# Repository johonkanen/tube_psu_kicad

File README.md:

# tube_psu_kicad

Migration of the **tube_power_5_1** board ("Tube power supply", V5.1) from Proteus 8.12
to KiCad 10. The KiCad schematic is redrawn from the Proteus PDF, and the PCB is rebuilt
from the Proteus gerbers, so that every pad, track, via and pour carries a net from the new
schematic. The goal is a KiCad design that is **electrically identical** to the Proteus
original.

The Proteus project file is binary and cannot be read, so the IPC-D-356A netlist in the
CADCAM export is the reference: 193 nets, 315 parts, 1165 pad/via/hole records, each with
net, refdes, pin and coordinates. Every check in this repo compares against that file.

The method follows `tools/p2k/CONVERSION_PLAYBOOK.md`. The tools are the shared
[proteus2kicad](https://github.com/johonkanen/proteus2kicad) repository, a git submodule in
`tools/p2k` (clone with `git clone --recurse-submodules`, or run
`git submodule update --init`); everything specific to this board is in `p2k_config.py`.

- `PLAN.md`: the plan, inventory of the source files, risks and model usage.
- `STATUS.md`: what is done, the last verification output, findings about the original
  design, and what comes next.
- `next_prompt.md`: the prompt for the next work session, replaced at the end of every
  phase.

## Board

3D renders and copper layers of the 5.2 board `kicad_next/tube_psu_5_2.kicad_pcb` (6 layers, in work) and of the
5.1 board `kicad/tube_psu.kicad_pcb`, made by GitHub Actions on every board change
([kicad-board-plots](https://github.com/johonkanen/kicad-board-plots), `.github/workflows/board-plots.yml`;
the images live on the `renders` branch).

<!-- board-plots:start -->
<!-- Generated by kicad-board-plots; edits between these markers are overwritten. -->

### tube_psu_5_2

3D renders and copper layers of `kicad_next/tube_psu_5_2.kicad_pcb`, the layers in stack order without silkscreen. Plotted by [kicad-board-plots](https://github.com/johonkanen/kicad-board-plots) on each board change; the images live on the `renders` branch.

<table>
<tr>
<td align="center"><br><b>3D, top</b></td>
<td align="center"><br><b>3D, bottom (seen from below)</b></td>
</tr>
<tr>
<td align="center"><br><b>F.Cu: signal, Net-(RL1-COM), HEATER_HI_SOURCE, DHB_HI_SOURCE, GND, Q14_DRAIN and 28 more pours (top)</b></td>
<td align="center"><br><b>In1.Cu: IN2, ISO_GND, HT_GND, GND, RES_IN planes</b></td>
</tr>
<tr>
<td align="center"><br><b>In2.Cu: signal</b></td>
<td align="center"><br><b>In3.Cu: signal + plane, 5V, 6V3, 5V_ISOL, 15V_ISO_SEC, 15V and 1 more pours</b></td>
</tr>
<tr>
<td align="center"><br><b>In4.Cu: IN2, ISO_GND, GND, HT_GND planes</b></td>
<td align="center"><br><b>B.Cu: signal, 420V, PFC CURRENT 2+, ISO_GND, GND, 6V3 and 5 more pours (bottom, seen from the top)</b></td>
</tr>
</table>

### tube_psu

3D renders and copper layers of `kicad/tube_psu.kicad_pcb`, the layers in stack order without silkscreen. Plotted by [kicad-board-plots](https://github.com/johonkanen/kicad-board-plots) on each board change; the images live on the `renders` branch.

<table>
<tr>
<td align="center"><br><b>3D, top</b></td>
<td align="center"><br><b>3D, bottom (seen from below)</b></td>
</tr>
<tr>
<td align="center"><br><b>F.Cu: signal, Net-(RL1-COM), HEATER_HI_SOURCE, GND, Q14_DRAIN, AC1 and 28 more pours (top)</b></td>
<td align="center"><br><b>In1.Cu: signal, Q14_DRAIN, HT_GND, IN2, GND, Net-(L2-2) and 5 more pours</b></td>
</tr>
<tr>
<td align="center"><br><b>In2.Cu: signal, GND, IN2, L2_PRI2, Q14_DRAIN, DHB_HI_SOURCE_SEC and 3 more pours</b></td>
<td align="center"><br><b>B.Cu: signal, 420V, PFC CURRENT 2+, GND, ISO_GND, 15V and 6 more pours (bottom, seen from the top)</b></td>
</tr>
</table>

<!-- board-plots:end -->

## Layout

```
source/      Proteus exports (read-only): schematic PDF + page renders + text, the .pdsprj,
             cadcam/ = Gerber X2 export with drill gerbers and IPC-D-356A netlist (used),
             cadcam_rs274x/ = earlier RS-274X export with Excellon drill (cross-check only)
reference/   tables generated from the IPC netlist: pads (CSV/JSON), pin→net per part,
             pins per net
lib/         tube_psu.kicad_sym, part_map.csv, footprint_map.csv, tube_psu.pretty/ (all generated)
kicad/       KiCad project: root sheet + 11 sub-sheets (one per PDF page), tube_psu.kicad_pcb
             (generated by tools/make_pcb.sh)
p2k_config.py  board configuration of the proteus2kicad tools
tools/       check_all.sh, erc.sh, make_part_map.py, gen_symbols.py, sheets/ (one script per
             sheet), gen_footprints.py, make_pcb.sh, measure_gaps.py; p2k/ = proteus2kicad submodule
reports/     generated reports
```

## Phases

| Phase | Content | State |
|---|---|---|
| 0 | Tooling: KiCad AppImage wrappers, IPC-D-356A parser, reference tables, X2 export check | done |
| 1 | Schematic: part map, symbols, netlist comparison, skeleton; 11 sheets redrawn | done |
| 2 | Footprints, fitted to the IPC pads | done |
| 3 | PCB: board, tracks/vias from gerbers, nets, zones, DRC | done |
| 4 | Independent verification: gerber round trip, IPC-D-356 diff | – |

## Checks

`tools/check_all.sh` runs every check and prints `ALL CHECKS PASSED` or the failing steps.

| Script | Checks |
|---|---|
| `tools/p2k/bin/p2k ipc356 --check` | IPC parser counts and fix-ups; reference tables up to date |
| `tools/p2k/bin/p2k check_sources` | Gerber X2 flashes (vias, pads, free pads, holes) and drills vs IPC; outline |
| `tools/make_part_map.py --check` | `lib/part_map.csv` up to date with the .pdsprj, PDF and IPC |
| `tools/gen_symbols.py --check` | `lib/tube_psu.kicad_sym` up to date |
| `tools/p2k/bin/p2k check_symbols` | symbol pin set = IPC pin set for every refdes |
| `tools/erc.sh` | KiCad ERC, 0 errors |
| `tools/p2k/bin/p2k compare_netlists` | schematic netlist vs IPC by pad sets (`--sheet N`, `--allow-missing` while drawing) |
| `tools/gen_footprints.py --check` | footprint map and `lib/tube_psu.pretty` up to date |
| `tools/p2k/bin/kipy -m p2k.check_footprints --pcbnew` | every footprint fits its IPC pads within 0.05 mm |
| `tools/make_pcb.sh --check` | the board rebuilt from scratch equals `kicad/tube_psu.kicad_pcb` byte for byte |
| `tools/p2k/bin/kipy -m p2k.check_board` | board pads, holes, free pads, vias vs IPC (position, size, net) |
| `tools/p2k/bin/kipy -m p2k.assign_nets --check` | copper connectivity after zone fill: 0 shorts / orphans / opens |
| `tools/p2k/bin/p2k drc` | KiCad DRC with schematic parity: 0 shorts / unconnected / parity, accepted types only |

`tools/p2k/bin/p2k ipc356` regenerates `reference/` after a change of `p2k_config.py`.

## KiCad environment

KiCad 10.0.7 AppImage at `~/kicad/kicad-10.0.7-x86_64.AppImage`. `tools/p2k/bin/kipy` (KiCad's
Python with `pcbnew`) and `tools/p2k/bin/kicad-cli` mount it on demand (`tools/p2k/bin/kicad_env.sh`).
Never run the AppImage with `--version`: it starts the GUI and hangs.

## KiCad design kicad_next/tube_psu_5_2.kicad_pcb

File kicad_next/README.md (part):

# kicad_next – tube_power 5.2 (KiCad project `tube_psu_5_2`)

The next board revision, forked from the verified 5.1 migration in `kicad/` (which stays frozen and is
checked by `tools/check_all.sh`). What changes is in [../NEXT_REVISION.md](../NEXT_REVISION.md), the
phases and decisions D1–D6 in [../NEXT_REVISION_PLAN.md](../NEXT_REVISION_PLAN.md).
State: **phase 3 done (2026-11-18)** – footprints and 3D models for every part, creepage slots (section
"Footprints and 3D models" below); **phase 2 done (2026-11-18)** – schematic changes of NEXT_REVISION.md applied (item-by-item list, open
questions and the generated netlist diff 5.1 → 5.2: [CHANGES_5_2.md](CHANGES_5_2.md)); phase 1 (2026-11-17):
6-layer board skeleton, stackup, JLC rules, net classes per isolation domain, creepage / clearance rules.

## What is where

| Path | Content | Made by |
|---|---|---|
| `kicad_next/tube_psu_5_2.kicad_pro` | project: ERC settings (as 5.1), net classes + netclass patterns (one per net), board minimums (JLC) | copied from 5.1 once; classes / rules by `tools/next/setup_project.py` |
| `kicad_next/tube_psu_5_2.kicad_sch` + `01_…11_*.kicad_sch` | schematic (root + 11 sheets) | `tools/next/gen_schematic.py` (do not edit by hand while the scripts are the source) |
| `kicad_next/tube_psu_5_2.kicad_pcb` | **the 5.2 board** (since 2026-11-20): placement of trial step 3 (all 375 footprints, slots, keep-outs, the kept 5.1 copper), 5.1 outline, H1–H8, 6 copper layers, JLC stackup; not routed yet | skeleton by `tools/next/make_board.py`, then `tools/next/promote_trial_board.py` (kipy) once from the step-3 trial board; **from here on edited in KiCad / by the routing (phase 5/6), only checked** |
| `kicad_next/tube_psu_5_2.kicad_dru` | custom rules: JLC limits, HV functional spacing, creepage / clearance between domains | by hand (this file is the source) |
| `kicad_next/sym-lib-table`, `fp-lib-table` | `tube_psu_next` → `lib/tube_psu_next.kicad_sym` (used), `tube_psu` → `lib/tube_psu.kicad_sym` (5.1, reference); footprints `tube_psu` → `lib/tube_psu.pretty`, `tube_psu_next` → `lib/tube_psu_next.pretty`, `tube_psu_next_parts` → `lib/tube_psu_next_parts.pretty` | `gen_schematic.py` |
| `tools/next/sheets/sheetNN.py`, `_common.py` | sheet scripts, copies of `tools/sheets/` (sheet scripts unchanged; `_common.py` redirects output, symbol library, CSVs) | phase 2 edits these |
| `tools/next/gen_symbols.py` → `lib/tube_psu_next.kicad_sym` | 5.2 symbols (fork of `tools/gen_symbols.py`; identical output at the fork) | phase 2 adds ICE5AR (PWM2, replaced the iW1819), SI8621, UCC21520, … |
| `lib/part_map_next.csv`, `lib/footprint_map_next.csv`, `lib/jlc_parts_next.csv` | values, footprints, LCSC numbers per refdes – hand-edited forks of the 5.1 tables | by hand |
| `tools/next/check_next.sh` | all 5.2 checks (below) | – |
| `tools/next/gen_next_footprints.py` → `lib/tube_psu_next.pretty` | EEL19 / EC42 transformers, L1/L2 upright toroid on the 5.1 RM8 holes (`_Vertical_RM8_45deg` / `_315deg`, 2026-11-19; the flat toroid + `_TieSlots` unused), heatsink outline helper | phase 3 |
| `tools/next/gen_next_footprints_parts.py` → `lib/tube_psu_next_parts.pretty` | SOIC-16W with creepage slot (`_Slot8.0`, `_Slot11.1`), electrolytics with the real can height (`_H<n>mm`), copies of 5.1 footprints with a 3D model (reads KiCad library footprints from the AppImage: run through `tools/p2k/bin/kicad_env.sh`) | phase 3 |
| `tools/next/gen_next_3d.py` → `lib/tube_psu_next.3dshapes` | 16 simple STEP models (CadQuery venv, see below) | phase 3 |
| `tools/next/reuse_51_board.py` (kipy) → `kicad_next/trial_from_51/` step 0, `tools/next/trial_placement.py` (kipy) → step 1, `tools/next/trial_placement_p2.py` (kipy) → step 2, `tools/next/trial_placement_p3.py` (kipy) → step 3, `tools/next/trial_report.py` → `REPORT.md` | trial 5.2 board from the verified 5.1 layout (step 0: footprints / nets / copper reuse, L1 / L2 upright on the RM8 holes); step 1: TR3 / split caps / DRV5 / DRV6 moves as data (`PLACE` / `GROUPS`) + split-pass DRC; step 2: UART island at the top edge, Q19 / Q21 / ISO2 L-slot, ISO2 / D4 / D5, TR1 / PWM2 / C102 flyback re-place, gate-driver bootstrap / decoupling parts (`PLACE` / `AUTO` / `GROUPS` / `SLOTS` / `KEEPOUTS`, deleted copper listed in `placement_p2.json`); step 3: heater barrier slot at ISO1 / TR2 + pour keep-outs, relay driver Q9 moved under RL1, PE / mounting-hole keep-outs and C85, the 54 added parts placed from the off-board grid (`PLACE` / `NEW` / `GROUPS` / `FOOTPRINTS` / `SLOTS` / `KEEPOUTS` / `DELETE` / `TEXTS`, ISO1 with its board-specific T-slot footprint, mounting-hole pad moves, deleted copper listed in `placement_p3.json`); the latest step is checked by `check_domains.py` in check_next.sh, its DRC only by the placement scripts | phase 5 input |
| `tools/next/check_domains.py` [BOARD] | isolation-domain distance check of a board (check_next.sh: the real board; default: the latest trial step): straight same-layer distance between pads / tracks / vias / filled zone copper of two domains and the mounting holes (PE), limits = the `.kicad_dru` rules, slot credit only where a slot blocks the straight line (path round the slots), accepted pairs in its commented `ALLOW` list; ≈ 10 s, a few hundred MB – KiCad's creepage DRC does not list every pair | phase 5 / 6 |
| `tools/next/promote_trial_board.py` (kipy) | copies `trial_from_51/tube_psu_5_2_trial_p3.kicad_pcb` to the real board, 3D model paths back to `${KIPRJMOD}/../lib`, Description / LCSC fields from the schematic (refuses to overwrite a populated board without `--force`) | phase 5 start |
| `tools/next/route_s2_planes.py` (kipy), `tools/next/render_inner_layers.py` | routing stage 2: inner-layer planes / pours `S2_*` of the real board (re-runnable, section "Inner layers (routing stage 2)"); PNGs of the inner layers in `kicad_next/routing/` | phase 6 |
| `tools/next/route_s3a_power.py`, `tools/next/s3_router.py` (python3 + kipy), `tools/next/render_s3a.py` | routing stage 3a: power / HV / ground copper as data (drawn tracks, zones `S3A_*`, vias, connections routed by a local grid router that keeps the class, HV and domain spacings), re-runnable (`routing/s3a_added.json`), PE pour keep-outs `S3A_KO_PE_*`; PNGs `routing/s3a_*.png` (section "Power, HV and ground routing (stage 3a)") | phase 6 |
| `tools/next/route_s3c_cleanup.py` | routing stage 3c: kept 5.1 copper that breaks the 5.2 HV spacing deleted and drawn again, dangling 5.1 copper deleted (`routing/deleted_s3c.json`, `s3c_added.json`); runs between stage 3a and stage 3b (section "Clean-up of the kept 5.1 copper (stage 3c)") | phase 6 |
| `tools/next/route_s3d_iso2.py` | routing stage 3d: ISO2 / AD2 fan-out on both sides as drawn copper, the 420V sense divider as a row with its feed, R10 / R79 moved (`routing/moves_s3d.json`, `deleted_s3d.json`, `s3d_added.json`); runs between stage 3c and stage 3b (section "ISO2 / AD2 fan-out (stage 3d)") | phase 6 |
| `tools/next/route_s3e_j2.py` | routing stage 3e: the J2 header escapes and the open nets that end at J2 as drawn copper - analog lines, the control bus round mounting hole H4, the DRV3 / DRV5 inputs, HT_SDATA at ISO1 (`routing/deleted_s3e.json`, `s3e_added.json`, `moves_s3e.json`); runs between stage 3d and stage 3b (section "J2 escapes and J2 nets (stage 3e)") | phase 6 |
| `tools/next/check_board.py` | DRC of the real board without the creepage pass (> 3 GB on the populated board) + `--schematic-parity`: fails on any parity item, short or isolation-rule violation besides `ACCEPTED`; everything else counted (`reports/next/drc.json`, ≈ 2.3 GB, 10 s) | phase 5 |
| `tools/next/check_footprints.py` | footprint / pad / 3D / barrier-creepage check (kipy), `--dump` for `render_footprints.py` (PNGs) | phase 3 |
| `tools/next/netlist_diff.py` | netlist diff 5.1 → 5.2 (section of CHANGES_5_2.md) + check that the three CSVs cover every part | phase 2 |
| `kicad_next/CHANGES_5_2.md` | phase-2 change list per NR item, open questions, netlist diff | phase 2 |

How the fork avoids touching shared code: `p2k.sheetkit.sheet()` hard-codes `kicad/`, and
`p2k.sch_builder` reads `lib/<PROJECT>.kicad_sym` / `lib/footprint_map.csv` of `p2k_config.py`.
`tools/next/sheets/_common.py` therefore defines its own `sheet()` (output `kicad_next/` or
`$TUBE_PSU_NEXT_OUT`, project `tube_psu_5_2`), replaces `sch_builder.lib` / `sch_builder.footprint` at module
level and wraps `Sheet.save` to rename the library nickname `tube_psu_5_2:` → `tube_psu_next:`. Symbol
UUIDs are seeded as in 5.1, so unchanged parts keep their 5.1 UUIDs. `tools/p2k`, `tools/sheets/`,
`kicad/` and the 5.1 `lib/` files are unchanged.

## Regenerate / check

```
python3 tools/next/gen_symbols.py                 # lib/tube_psu_next.kicad_sym (after editing build())
python3 tools/next/gen_schematic.py               # kicad_next/*.kicad_sch from tools/next/sheets
python3 tools/next/setup_project.py               # net classes / domains / board minimums -> .kicad_pro
python3 tools/next/setup_project.py --list        # every net with its class
tools/next/check_next.sh                          # everything below, prints ALL 5.2 CHECKS PASSED
```

`check_next.sh` steps: symbol library up to date; schematic regenerated in a temporary directory equals
`kicad_next/` byte for byte; part footprints up to date; ERC (0 errors / 15 warnings: 12 isolated_pin_label +
3 ground_pin_not_ground on the UCC21520 high-side VSSA pins 14 of DRV5, DRV6 and DRV3; was 14 / 2 before DRV3 became a UCC21520); every net in
exactly one isolation domain and the project file up to date; board skeleton (6 layers, names / types,
stackup thicknesses, outline and H1–H8 equal to `kicad/tube_psu.kicad_pcb`); DRC 0 violations;
`check_rules.py` – kicad-cli silently drops a broken `.kicad_dru` rule, so 13 pairs of test tracks are
added to a temporary copy of the board and the DRC must report exactly the expected violation at each
(creepage 11.1 / 8.0 / 4.2 / 3.2 mm, inner-layer 11.1 / 8.0 mm, clearance 4.0 mm, HV functional 1.2 mm,
mounting hole; phase 2 adds 4 UART-island cases: 19 in total); `netlist_diff.py --check` (CHANGES_5_2.md netlist
section up to date, every part in the three CSVs with the schematic value / footprint). Phase 3 adds:
`gen_next_footprints.py --check`, `gen_next_footprints_parts.py --check`, `gen_next_3d.py --check` (only if
CadQuery is found at `$CQ_PYTHON` or `~/.venvs/cq/bin/python`, else skipped) and `check_footprints.py`.
Trial placement step 3 (2026-11-19) adds: 3 pad tests in `check_rules.py` (VSSOP-8 pads 0.15 mm apart: allowed
on low-voltage nets by the rule "Same-footprint pad gap, low-voltage classes", still a clearance violation on a
HV net; 22 tests in total); `check_footprints.py` also checks the board-specific footprint variants
(`BOARD_VARIANTS`: ISO1 with the T slot, non-convex slot outlines handled exactly); and `check_domains.py` on the
board (the latest trial board until 2026-11-20, now `kicad_next/tube_psu_5_2.kicad_pcb`) – every pair of copper items of two isolation domains on the same layer against the
clearance / creepage / inner-layer limits of the `.kicad_dru` (table `LIMITS`), with slot credit only where a
slot blocks the straight line; exit status 1 on any pair below its limit that is not in its `ALLOW` list (empty
since routing stage 4k; it held the Q19 / Q21 slot exception and the TR1 pin 2 / 9 barrels). Stage 1 of the routing (2026-11-20, the trial board
becomes the real board) replaces the plain DRC step (0 violations required, full creepage DRC) by `check_board.py`
and lets `make_board.py --check` accept internal Edge.Cuts slots inside the unchanged 5.1 outline.

## First draft (2026-11-22)

State after the clean-up pass `tools/next/route_s6_cleanup.py --group clr,dangling` (stage 6; incremental, not
re-runnable; `routing/deleted_s6.json`, `s6_added.json`, `moves_s6.json` (empty)): every connection of the netlist is
made, 0 shorts, 0 unconnected, `tools/next/check_next.sh` passes. This is the first complete draft, not a board
checked for ordering. No part moved in this pass. PNGs of all six copper layers of this state: `routing/s3a_F_Cu.png`,
`s3a_B_Cu.png`, `In1_GND.png` ... `In4_GND.png`, overviews `inner_domains.png`, `s3a_power_nets.png`
(`render_s3a.py`, `render_inner_layers.py`).

### DRC (check_board.py, without the creepage pass and without silkscreen checks)

| type | before | now | what is left and why |
|---|---|---|---|
| shorts / unconnected / parity | 0 | 0 | |
| clearance | 5 (7 with `--all-track-errors`) | 0 | Net class gaps 0.2 mm that were 0.16 ... 0.175 mm: EPWM5A_ISO In2 diagonal 0.09 mm further from the EPWM6A_ISO via (-48.89, -54.21); 5V on B.Cu 0.045 mm west (x -59.745, y -33.0 ... -26.5) past the pads of D9 and D28 pad A (two of the three pads were hidden behind the first marker); GND via (27.1, 5.1) -> (27.15, 5.1); Net-(C11-Pad1) via (28.4, 7.7) -> (28.45, 7.7); GND via (4.45, -56.9) -> (4.45, -56.95). The Net-(C11-Pad1) via now has 0.204 / 0.213 / 0.204 mm to the +1V65_BIAS track (F.Cu), R65 pad 2 and the Net-(C127-Pad1) track (B.Cu). |
| track_dangling | 26 | 0 | Pieces under / inside a wider track of the same net, zero-length segments, overshoots trimmed to the via / junction, and stubs to nothing (5.1 leftovers of moved parts) deleted back to the next junction, with two vias that only fed such a stub (15V (15.24, -35.02), 5V (-23.9, -53.036) with its In2 lane). The longest: a +3V3 In2 lane of 25 mm from (34.2, -28.6) to a free end at (16.8, -48.4), and a +3V3 In2 stub at the via (5.8, -60.1). The DC+ track of C47 ended in a round hole of 'Proteus F.Cu pour 29' at (45.62, -41.95); it now ends inside the fill at y -42.7. |
| courtyards_overlap | 132 | 132 | Classified by pad bounding boxes and F.Fab / B.Fab body boxes: 106 pairs stand at their 5.1 place (same relative place, side and turn; 17 of them with overlapping body boxes - film / electrolytic capacitors beside C86, C117, C37, C31 / C32 and the paralleled capacitors C99 / C100 / C101, C90 / C91 on the 420V rail. Correction (stage 7): those five were NOT as in 5.1 - change 5.6 made them 1210 (5.1: 1206) at the old 2.0 / 1.9 mm pitch, the bodies overlapped 0.5 / 0.6 mm; re-spaced in stage 7); 26 pairs are new or changed and courtyard-only (pads of two nets >= 0.238 mm apart, no body box overlap > 0.05 mm; same-net pads touch at C124 / R70, R90 / D34, R79 / R49, R90 / R70). No pair with a new pad or body collision, so no part was moved. |
| pth_inside_courtyard | 2 | 2 | Pin 1 of IN1 and pin 3 of CM1 inside the courtyard of the film capacitor C86 - as in 5.1 (the three parts are where they were). |
| starved_thermal | 2 | 2 | C102 pin 1 (ISO_GND, (77.0, 13.85)) on In1 and In4: the pin stands in a 1.5 mm neck of the ISO_GND plane, one spoke north and one south. The barrel joins both; bias capacitor, no current. Not changed (a solid connection of this pad was not tried to the end). |
| lib_footprint_mismatch | 2 | 2 | Q19 and Q21 (TO-220-3_Vertical): the board copies differ from the library footprint. Looked into in the verification: only the pad option 'remove unused inner-layer rings' differs (set on purpose, `trial_placement_p2.py`); ignored by `check_board.py` since stage 7. Packages: Q7 / Q8 / Q19 / Q21 (STF7N60M2) are TO-220, pin pitch 2.54 mm; only Q5 / Q6 are TO-247 - earlier notes that took Q7 / Q19 for TO-247 are wrong. |

### Not checked

* The creepage DRC pass of KiCad over the whole board (needs > 3 GB); the isolation distances are checked by
  `check_domains.py` only.
* Signal integrity of the UART pair: 82 mm on In3 between the pads of L2 and beside / under the power stages.
* The via-in-pad process. 71 vias lie in or touch an SMD pad of their own net (47 with the centre inside the pad):
  Q1 pad 3 (12), Q2 pad 3 (16), C73 pad 2 (10: 5 inside, 5 on the edge), C57 pad 2 (2), C89 pad 1 (2), R93 pad 2 (3),
  one via shared by C67 pad 1 / C70 pad 1 (18.3, -48.5) and one by D10 pad A / R142 pad 2 (36.8, 3.2), and one each
  at AD1 pad 3, AD2 pad 3, C125 pad 2, C139 pad 1, C22 pad 1, C27 pad 1, C68 pad 2, C79 pad 2, C80 pad 2, C95 pads 1
  and 2, DRV2 pad 1, DRV5 pad 11, Q9 pad 1, Q10 pad 1, R103 pad 1, R128 pad 1, R142 pad 1, R21 pad 1, R51 pad 2,
  R54 pad 2, R83 pad 1, R89 pad 1, U1 pad 4. Open: plugged vias at JLC or move them.
* Tight spots that pass: round DRV5 (x -10 ... 20, y -60 ... -40) the In2 control bus (nine lanes, 0.152 mm gaps
  for the 0.15 mm inner rule) and the four In3 lanes in the 15V window (0.158 mm) are at the rule by design; the
  +1V65_BIAS via (13.0, -44.076) is 0.164 mm from the $HT_CS and SYNCH_2 lanes. None was nudged (each lane has a
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
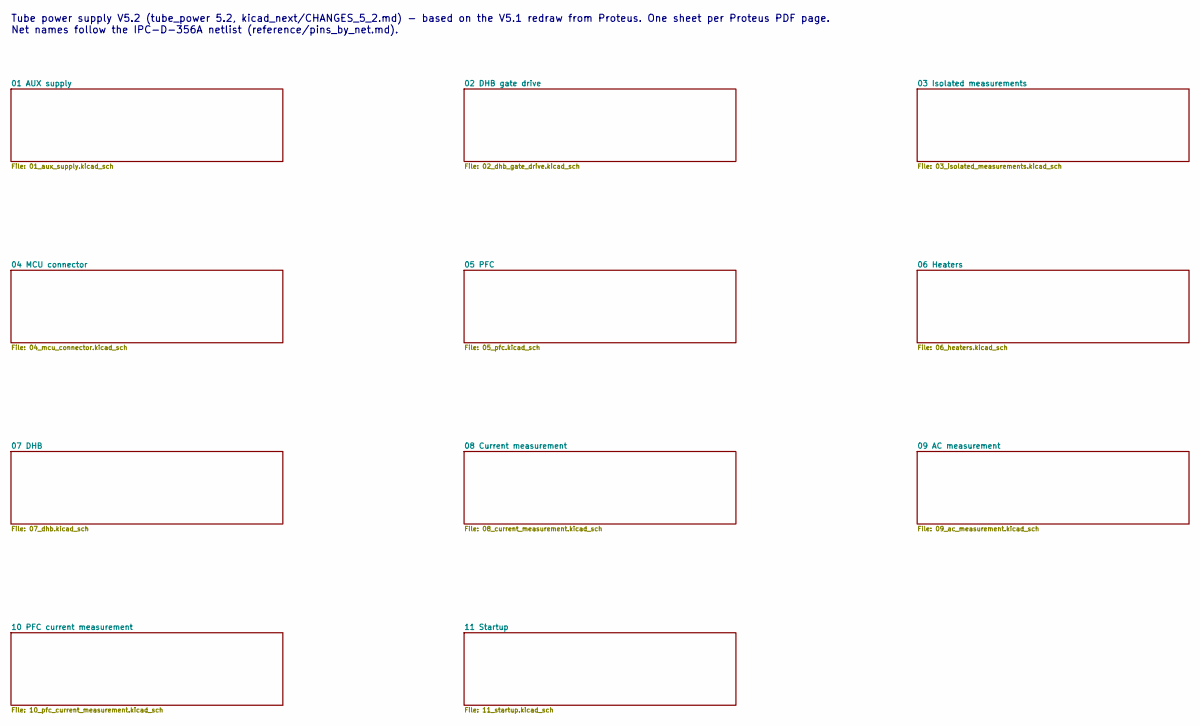
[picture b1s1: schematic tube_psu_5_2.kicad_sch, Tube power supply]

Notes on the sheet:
Tube power supply V5.2 (tube_power 5.2, kicad_next/CHANGES_5_2.md) - based on the V5.1 redraw from Proteus. One sheet per Proteus PDF page. Net names follow the IPC-D-356A netlist (reference/pins_by_net.md).

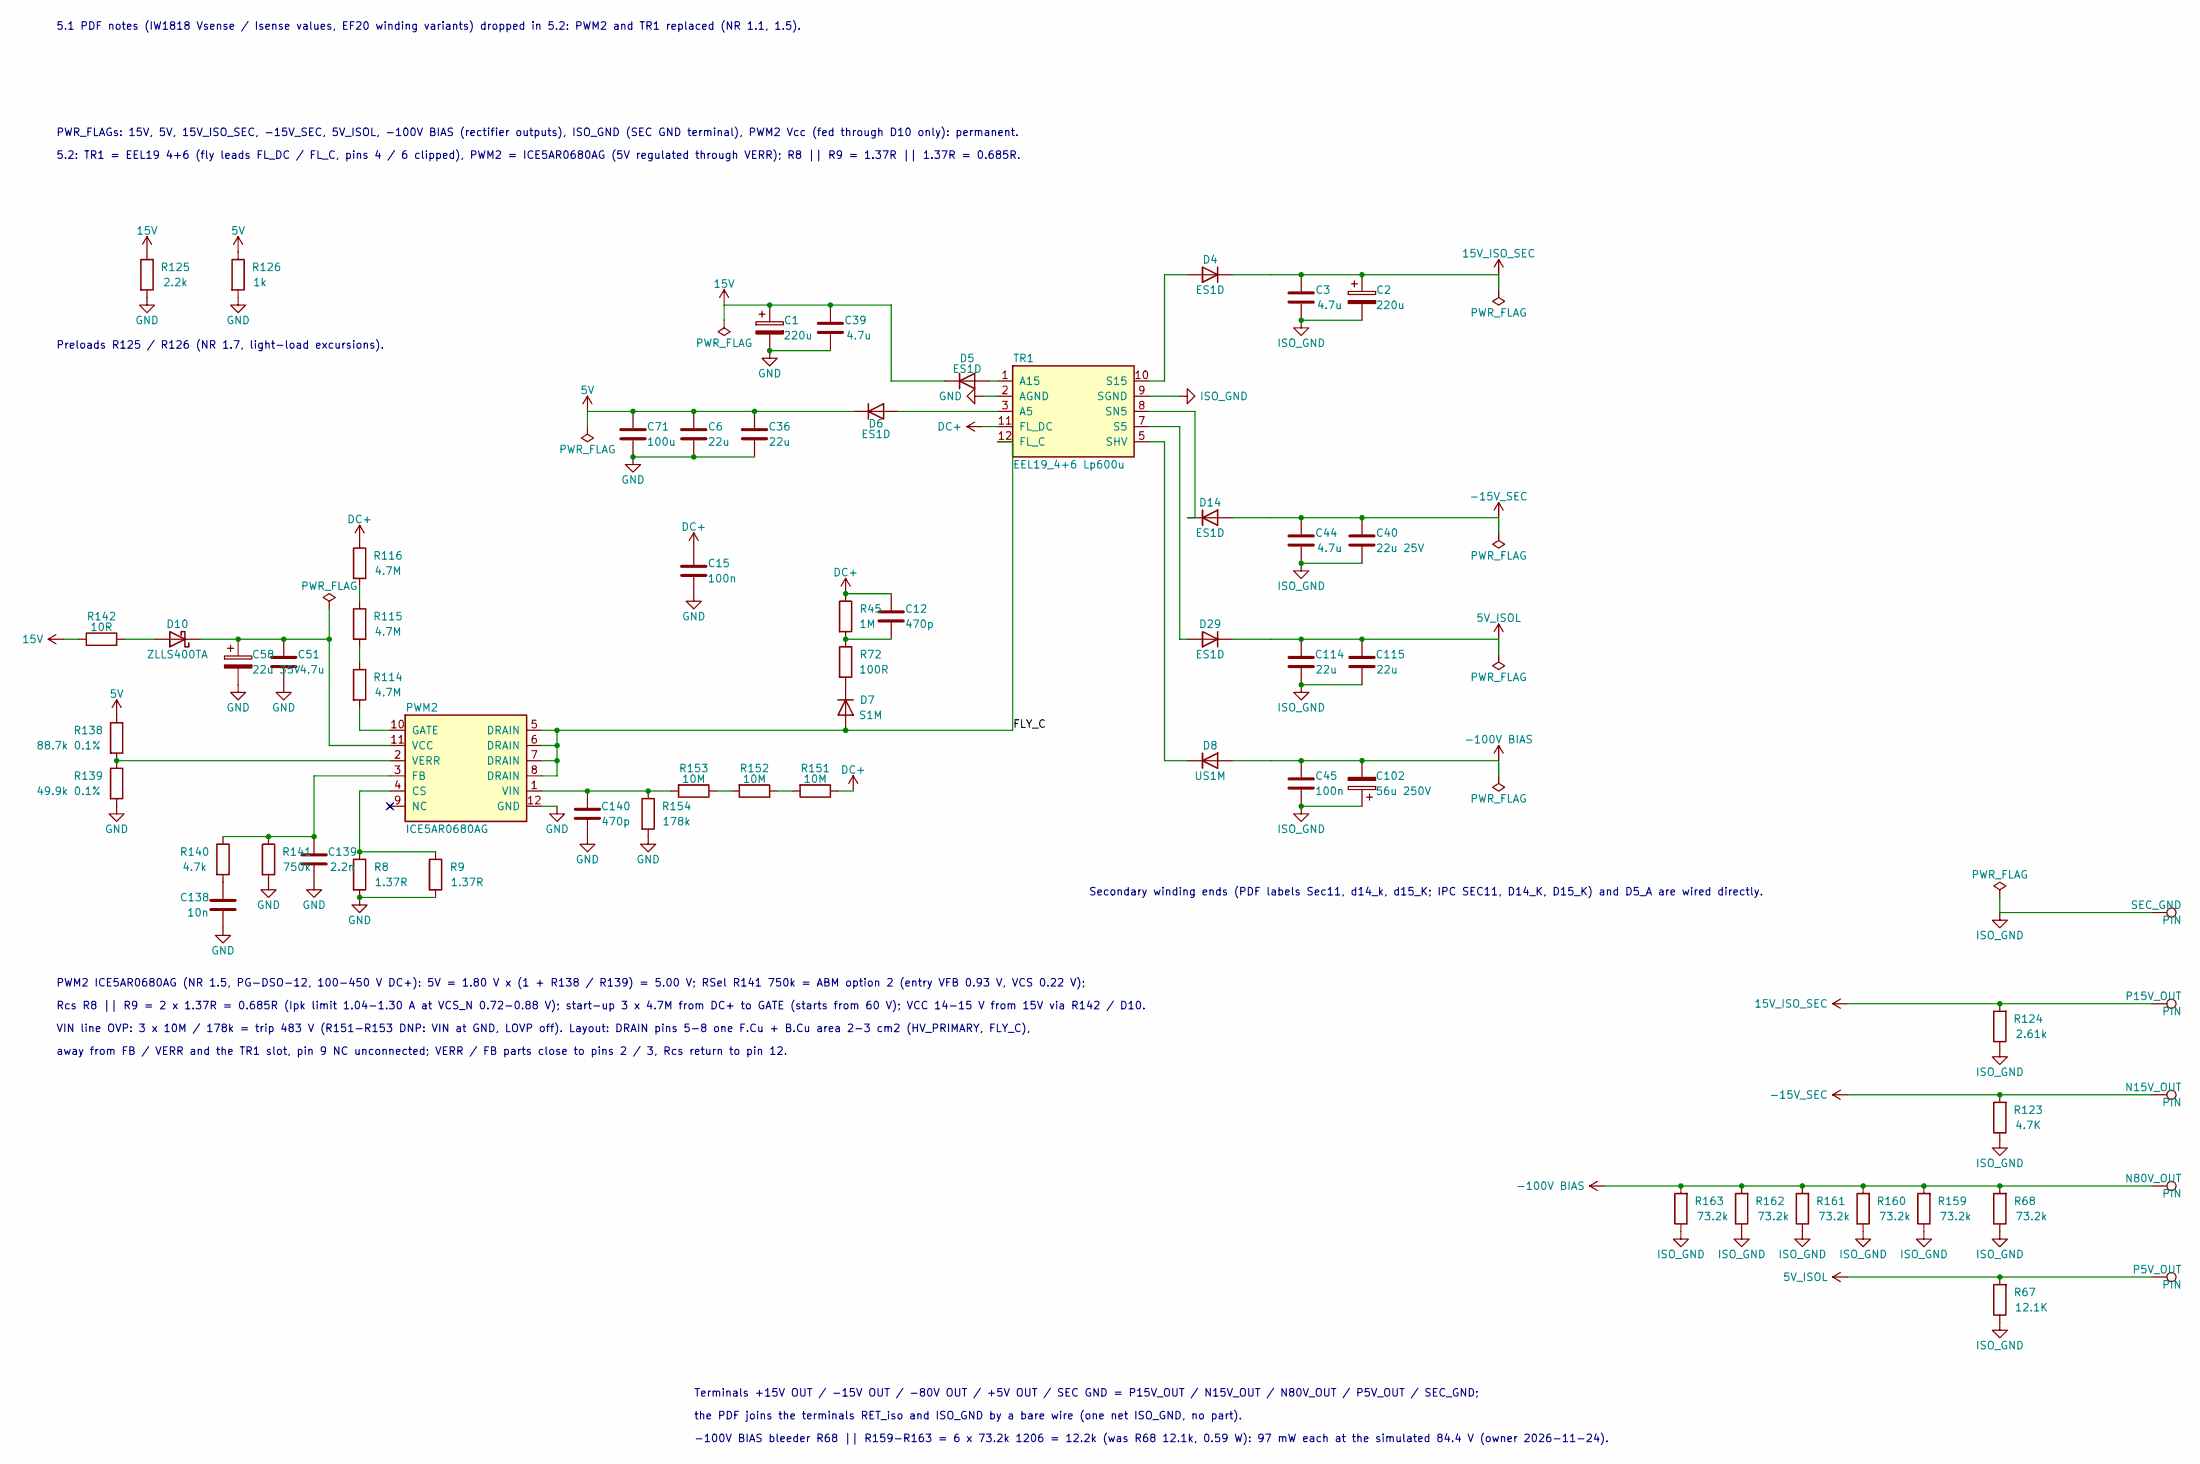
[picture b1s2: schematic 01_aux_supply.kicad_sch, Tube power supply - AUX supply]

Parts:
C1, C2: 220u; CP_Elec_6.3x7.7_EEEFTE221XAP; LCSC C190724
C3, C39, C44, C51: 4.7u; C_1206_3216Metric_Pad1.33x1.80mm_HandSolder; LCSC C29823
C6, C36, C114, C115: 22u; C_1206_3216Metric_Pad1.33x1.80mm_HandSolder; LCSC C12891
C12: 470p; C_1206_3216Metric_Pad1.33x1.80mm_HandSolder; LCSC C107177
C15, C45: 100n; C_1210_3225Metric; LCSC C692295
C40: 22u 25V; C_1206_3216Metric_Pad1.33x1.80mm_HandSolder; LCSC C12891
C58: 22u 35V; CP_Elec_5x5.4; LCSC C2887274
C71: 100u; C_1206_3216Metric_Pad1.33x1.80mm_HandSolder; LCSC C6119961
C102: 56u 250V; CP_Radial_D10.0mm_P5.00mm_H18mm; LCSC C22464691
C138: 10n; C_0603_1608Metric; LCSC C57112
C139: 2.2n; C_0603_1608Metric; LCSC C1604
C140: 470p; C_0603_1608Metric; LCSC C1620
D4, D5, D6, D14, D29: ES1D; D_SMA_AC; LCSC C116492
D7: S1M; D_SMA_AC; LCSC C64915
D8: US1M; D_SMA_AC; LCSC C412437
D10: ZLLS400TA; D_SOD-323_AC; LCSC C460267
N15V_OUT, N80V_OUT: PIN; Terminal_2x1_P5.00mm_D2.0mm_Drill1.4mm
P5V_OUT, P15V_OUT: PIN; Terminal_2x1_P5.00mm_D2.0mm_Drill1.4mm
PWM2: ICE5AR0680AG; PG-DSO-12_3.9x9.9mm_P1.27mm; LCSC C17699638
R8, R9: 1.37R; R_1206_3216Metric; LCSC C3000600
R45: 1M; R_1206_3216Metric; LCSC C17927
R67: 12.1K; R_1206_3216Metric; LCSC C247391
R68, R159, R160, R161, R162, R163: 73.2k; R_1206_3216Metric; LCSC C368302
R72: 100R; R_1206_3216Metric; LCSC C17901
R114, R115, R116: 4.7M; R_1206_3216Metric; LCSC C37800
R123: 4.7K; R_1206_3216Metric; LCSC C17936
R124: 2.61k; R_1206_3216Metric; LCSC C245506
R125: 2.2k; R_1206_3216Metric; LCSC C17948
R126: 1k; R_0805_2012Metric; LCSC C17513
R138: 88.7k 0.1%; R_0603_1608Metric; LCSC C728599
R139: 49.9k 0.1%; R_0603_1608Metric; LCSC C705780
R140: 4.7k; R_0603_1608Metric; LCSC C23162
R141: 750k; R_0603_1608Metric; LCSC C23240
R142: 10R; R_0603_1608Metric; LCSC C22859
R151, R152, R153: 10M; R_1206_3216Metric; LCSC C26119
R154: 178k; R_0603_1608Metric; LCSC C22823
SEC_GND: PIN; Terminal_2x1_P5.00mm_D2.0mm_Drill1.4mm
TR1: EEL19_4+6 Lp600u; Transformer_EEL19_V_4+6_FlyLeads

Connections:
5V: C6.2, C36.2, C71.2, D6.C (K), R126.1, R138.1; also elsewhere on the board
5V_ISOL: C114.1, C115.1, D29.C (K), P5V_OUT.1, R67.2; also elsewhere on the board
15V: C1.1, C39.1, D5.C (K), R125.1, R142.1; also elsewhere on the board
15V_ISO_SEC: C2.1, C3.1, D4.C (K), P15V_OUT.1, R124.2; also elsewhere on the board
-15V_SEC: C40.2, C44.2, D14.A, N15V_OUT.1, R123.2
-100V BIAS: C45.2, C102.2, D8.A, N80V_OUT.1, R68.2, R159.2, R160.2, R161.2, R162.2, R163.2
/01 AUX supply/FLY_C: D7.A, PWM2.5 (DRAIN), PWM2.6 (DRAIN), PWM2.7 (DRAIN), PWM2.8 (DRAIN), TR1.12 (FL_C)
DC+: C12.1, C15.2, R45.1, R116.1, R151.1, TR1.11 (FL_DC); also elsewhere on the board
GND: C1.2, C6.1, C15.1, C36.1, C39.2, C51.2, C58.2, C71.1, C138.2, C139.2, C140.2, PWM2.12 (GND), R8.2, R9.2, R125.2, R126.2, R139.2, R141.2, R154.2, TR1.2 (AGND); also elsewhere on the board
ISO_GND: C2.2, C3.2, C40.1, C44.1, C45.1, C102.1, C114.2, C115.2, R67.1, R68.1, R123.1, R124.1, R159.1, R160.1, R161.1, R162.1, R163.1, SEC_GND.1, TR1.9 (SGND); also elsewhere on the board
unnamed: C12.2, R45.2, R72.1
unnamed: C138.1, R140.2
unnamed: D7.C (K), R72.2
unnamed: D8.C (K), TR1.5 (SHV)
unnamed: C51.1, C58.1, D10.C (K), PWM2.11 (VCC)
unnamed: D10.A, R142.2
unnamed: D14.C (K), TR1.8 (SN5)
unnamed: PWM2.4 (CS), R8.1, R9.1
unnamed: C139.1, PWM2.3 (FB), R140.1, R141.1
unnamed: PWM2.10 (GATE), R114.2
unnamed: PWM2.2 (VERR), R138.2, R139.1
unnamed: C140.1, PWM2.1 (VIN), R153.2, R154.1
unnamed: R114.1, R115.2
unnamed: R115.1, R116.2
unnamed: R151.2, R152.1
unnamed: R152.2, R153.1
unnamed: D6.A, TR1.3 (A5)
unnamed: D5.A, TR1.1 (A15)
unnamed: D29.A, TR1.7 (S5)
unnamed: D4.A, TR1.10 (S15)

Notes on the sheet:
PWM2 ICE5AR0680AG (NR 1.5, PG-DSO-12, 100-450 V DC+): 5V = 1.80 V x (1 + R138 / R139) = 5.00 V; RSel R141 750k = ABM option 2 (entry VFB 0.93 V, VCS 0.22 V);
Rcs R8 || R9 = 2 x 1.37R = 0.685R (Ipk limit 1.04-1.30 A at VCS_N 0.72-0.88 V); start-up 3 x 4.7M from DC+ to GATE (starts from 60 V); VCC 14-15 V from 15V via R142 / D10.
VIN line OVP: 3 x 10M / 178k = trip 483 V (R151-R153 DNP: VIN at GND, LOVP off). Layout: DRAIN pins 5-8 one F.Cu + B.Cu area 2-3 cm2 (HV_PRIMARY, FLY_C),
away from FB / VERR and the TR1 slot, pin 9 NC unconnected; VERR / FB parts close to pins 2 / 3, Rcs return to pin 12.
Preloads R125 / R126 (NR 1.7, light-load excursions).
Secondary winding ends (PDF labels Sec11, d14_k, d15_K; IPC SEC11, D14_K, D15_K) and D5_A are wired directly.
Terminals +15V OUT / -15V OUT / -80V OUT / +5V OUT / SEC GND = P15V_OUT / N15V_OUT / N80V_OUT / P5V_OUT / SEC_GND;
the PDF joins the terminals RET_iso and ISO_GND by a bare wire (one net ISO_GND, no part).
-100V BIAS bleeder R68 || R159-R163 = 6 x 73.2k 1206 = 12.2k (was R68 12.1k, 0.59 W): 97 mW each at the simulated 84.4 V (owner 2026-11-24).
5.2: TR1 = EEL19 4+6 (fly leads FL_DC / FL_C, pins 4 / 6 clipped), PWM2 = ICE5AR0680AG (5V regulated through VERR); R8 || R9 = 1.37R || 1.37R = 0.685R.
5.1 PDF notes (IW1818 Vsense / Isense values, EF20 winding variants) dropped in 5.2: PWM2 and TR1 replaced (NR 1.1, 1.5).
PWR_FLAGs: 15V, 5V, 15V_ISO_SEC, -15V_SEC, 5V_ISOL, -100V BIAS (rectifier outputs), ISO_GND (SEC GND terminal), PWM2 Vcc (fed through D10 only): permanent.

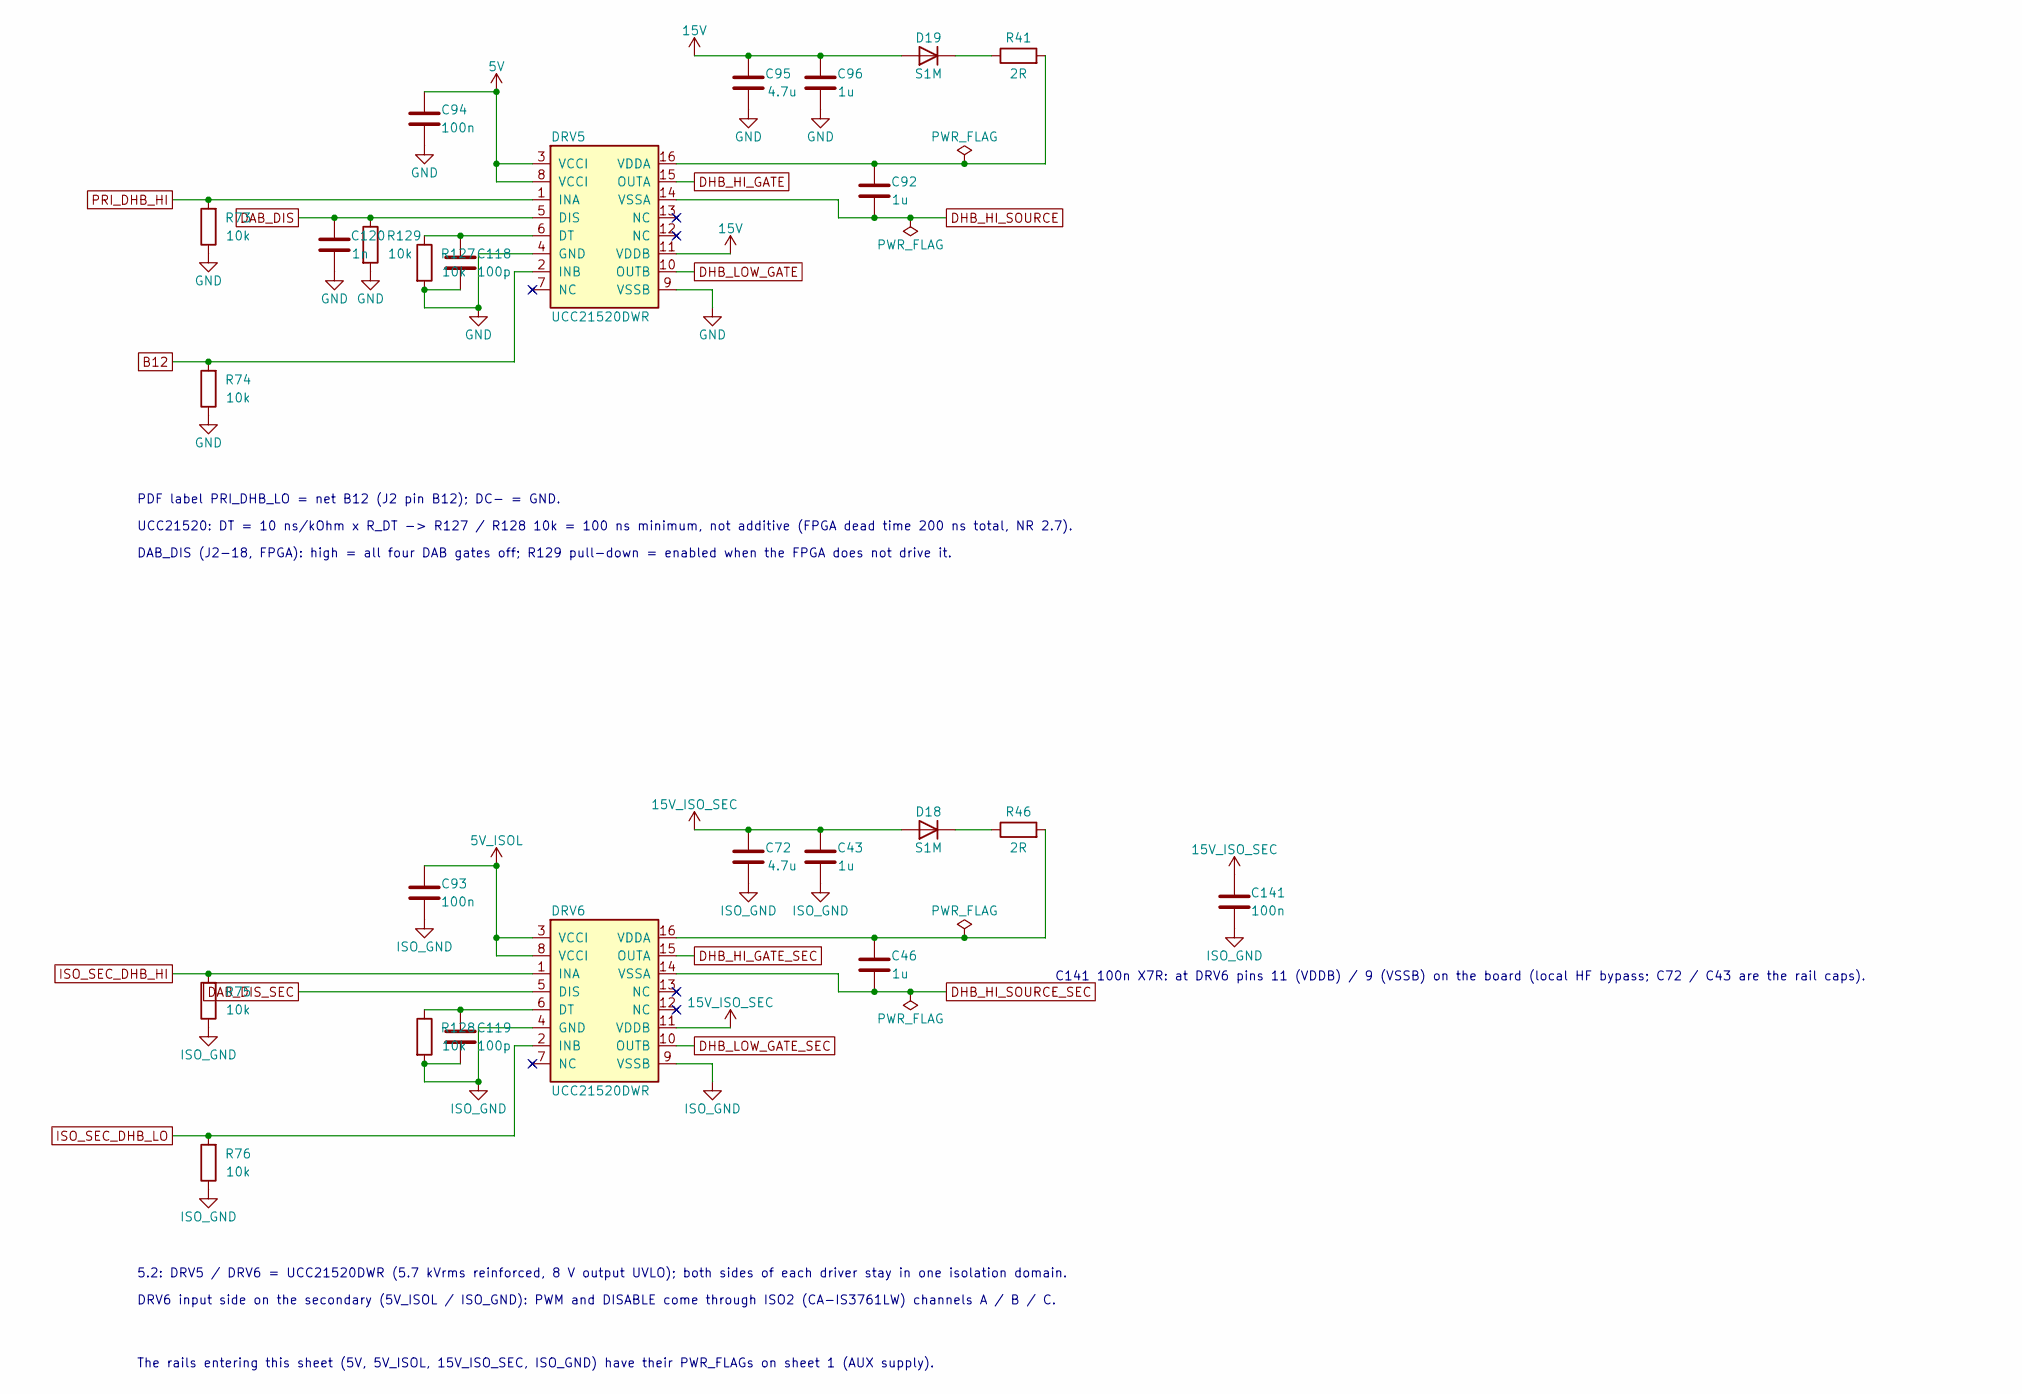
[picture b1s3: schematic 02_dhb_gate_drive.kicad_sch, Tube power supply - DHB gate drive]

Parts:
C43: 1u; C_0603_1608Metric; LCSC C15849
C46, C96: 1u; C_1206_3216Metric_Pad1.33x1.80mm_HandSolder; LCSC C1848
C72: 4.7u; C_1206_3216Metric_Pad1.33x1.80mm_HandSolder; LCSC C29823
C92: 1u; C_1206_3216Metric_Proteus3.15; LCSC C1848
C93, C94, C141: 100n; C_0603_1608Metric; LCSC C14663
C95: 4.7u; C_0603_1608Metric; LCSC C6119856
C118, C119: 100p; C_0603_1608Metric; LCSC C14858
C120: 1n; C_0603_1608Metric; LCSC C106246
D18, D19: S1M; D_SMA_AC; LCSC C64915
DRV5, DRV6: UCC21520DWR; SOIC-16W_7.5x10.3mm_P1.27mm; LCSC C601651
R41, R46: 2R; R_1206_3216Metric; LCSC C2907381
R73, R74, R75, R76, R127, R128, R129: 10k; R_0603_1608Metric; LCSC C25804

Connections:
5V: C94.1, DRV5.3 (VCCI), DRV5.8 (VCCI); also elsewhere on the board
5V_ISOL: C93.1, DRV6.3 (VCCI), DRV6.8 (VCCI); also elsewhere on the board
15V: C95.2, C96.1, D19.A, DRV5.11 (VDDB); also elsewhere on the board
15V_ISO_SEC: C43.2, C72.2, C141.1, D18.A, DRV6.11 (VDDB); also elsewhere on the board
B12: DRV5.2 (INB), R74.2; also elsewhere on the board
DAB_DIS: C120.1, DRV5.5 (DIS), R129.1; also elsewhere on the board
DAB_DIS_SEC: DRV6.5 (DIS); also elsewhere on the board
DHB_HI_GATE: DRV5.15 (OUTA); also elsewhere on the board
DHB_HI_GATE_SEC: DRV6.15 (OUTA); also elsewhere on the board
DHB_HI_SOURCE: C92.1, DRV5.14 (VSSA); also elsewhere on the board
DHB_HI_SOURCE_SEC: C46.1, DRV6.14 (VSSA); also elsewhere on the board
DHB_LOW_GATE: DRV5.10 (OUTB); also elsewhere on the board
DHB_LOW_GATE_SEC: DRV6.10 (OUTB); also elsewhere on the board
GND: C94.2, C95.1, C96.2, C118.2, C120.2, DRV5.4 (GND), DRV5.9 (VSSB), R73.1, R74.1, R127.2, R129.2; also elsewhere on the board
ISO_GND: C43.1, C72.1, C93.2, C119.2, C141.2, DRV6.4 (GND), DRV6.9 (VSSB), R75.1, R76.1, R128.2; also elsewhere on the board
ISO_SEC_DHB_HI: DRV6.1 (INA), R75.2; also elsewhere on the board
ISO_SEC_DHB_LO: DRV6.2 (INB), R76.2; also elsewhere on the board
unnamed: D18.C (K), R46.1
unnamed: D19.C (K), R41.1
unnamed: C118.1, DRV5.6 (DT), R127.1
unnamed: C92.2, DRV5.16 (VDDA), R41.2
unnamed: C119.1, DRV6.6 (DT), R128.1
unnamed: C46.2, DRV6.16 (VDDA), R46.2
PRI_DHB_HI: DRV5.1 (INA), R73.2; also elsewhere on the board

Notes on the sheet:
PDF label PRI_DHB_LO = net B12 (J2 pin B12); DC- = GND.
UCC21520: DT = 10 ns/kOhm x R_DT -> R127 / R128 10k = 100 ns minimum, not additive (FPGA dead time 200 ns total, NR 2.7).
DAB_DIS (J2-18, FPGA): high = all four DAB gates off; R129 pull-down = enabled when the FPGA does not drive it.
C141 100n X7R: at DRV6 pins 11 (VDDB) / 9 (VSSB) on the board (local HF bypass; C72 / C43 are the rail caps).
5.2: DRV5 / DRV6 = UCC21520DWR (5.7 kVrms reinforced, 8 V output UVLO); both sides of each driver stay in one isolation domain.
DRV6 input side on the secondary (5V_ISOL / ISO_GND): PWM and DISABLE come through ISO2 (CA-IS3761LW) channels A / B / C.
The rails entering this sheet (5V, 5V_ISOL, 15V_ISO_SEC, ISO_GND) have their PWR_FLAGs on sheet 1 (AUX supply).

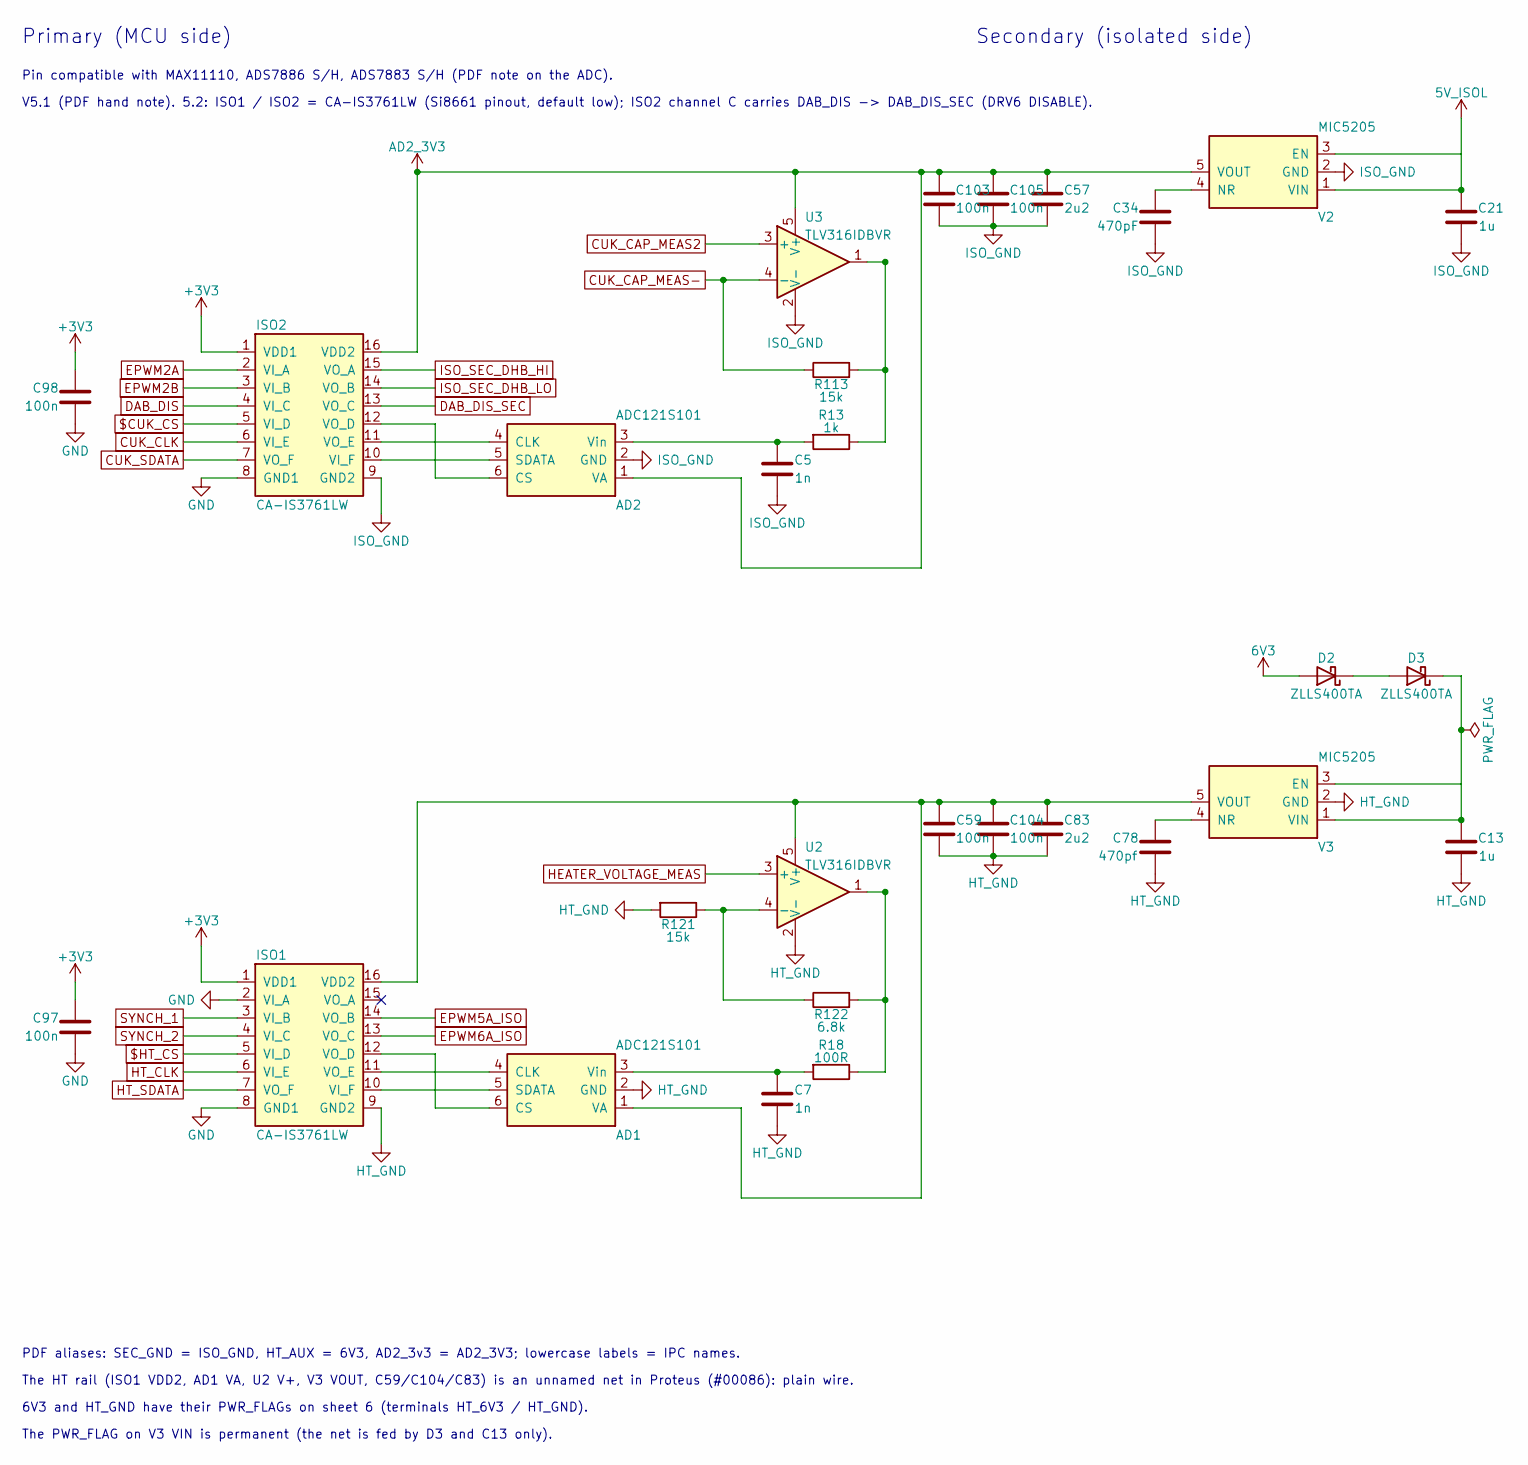
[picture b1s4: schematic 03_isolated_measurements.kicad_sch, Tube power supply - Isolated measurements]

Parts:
AD1, AD2: ADC121S101; SOT-23-6_Proteus; LCSC C74860
C5, C7: 1n; C_0603_1608Metric; LCSC C106246
C13, C21: 1u; C_0603_1608Metric; LCSC C15849
C34: 470pF; C_0603_1608Metric; LCSC C106211
C57, C83: 2u2; C_0603_1608Metric; LCSC C23630
C59, C97, C98, C103, C104, C105: 100n; C_0603_1608Metric; LCSC C14663
C78: 470pf; C_0603_1608Metric; LCSC C106211
D2, D3: ZLLS400TA; D_SOD-323_AC; LCSC C460267
ISO1: CA-IS3761LW; SOIC-16W_7.5x10.3mm_P1.27mm_Slot8.0_T_ISO1; LCSC C528659
ISO2: CA-IS3761LW; SOIC-16W_7.5x10.3mm_P1.27mm_Slot11.1; LCSC C528659
R13: 1k; R_0603_1608Metric; LCSC C21190
R18: 100R; R_0603_1608Metric; LCSC C22775
R113, R121: 15k; R_0603_1608Metric; LCSC C22809
R122: 6.8k; R_0603_1608Metric; LCSC C23212
U2, U3: TLV316IDBVR; SOT-23-5_Proteus; LCSC C575578
V2, V3: MIC5205; SOT-23-5_Proteus; LCSC C37970

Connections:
5V_ISOL: C21.1, V2.1 (VIN), V2.3 (EN); also elsewhere on the board
6V3: D2.A; also elsewhere on the board
$CUK_CS: ISO2.5 (VI_D); also elsewhere on the board
$HT_CS: ISO1.5 (VI_D); also elsewhere on the board
+3V3: C97.1, C98.1, ISO1.1 (VDD1), ISO2.1 (VDD1); also elsewhere on the board
AD2_3V3: AD2.1 (VA), C57.1, C103.1, C105.1, ISO2.16 (VDD2), U3.5 (V+), V2.5 (VOUT)
CUK_CAP_MEAS2: U3.3 (+); also elsewhere on the board
CUK_CAP_MEAS-: R113.1, U3.4 (-); also elsewhere on the board
CUK_CLK: ISO2.6 (VI_E); also elsewhere on the board
CUK_SDATA: ISO2.7 (VO_F); also elsewhere on the board
DAB_DIS: ISO2.4 (VI_C); also elsewhere on the board
DAB_DIS_SEC: ISO2.13 (VO_C); also elsewhere on the board
EPWM2A: ISO2.2 (VI_A); also elsewhere on the board
EPWM2B: ISO2.3 (VI_B); also elsewhere on the board
EPWM5A_ISO: ISO1.14 (VO_B); also elsewhere on the board
EPWM6A_ISO: ISO1.13 (VO_C); also elsewhere on the board
GND: C97.2, C98.2, ISO1.2 (VI_A), ISO1.8 (GND1), ISO2.8 (GND1); also elsewhere on the board
HEATER_VOLTAGE_MEAS: U2.3 (+); also elsewhere on the board
HT_CLK: ISO1.6 (VI_E); also elsewhere on the board
HT_GND: AD1.2 (GND), C7.2, C13.2, C59.2, C78.2, C83.2, C104.2, ISO1.9 (GND2), R121.2, U2.2 (V-), V3.2 (GND); also elsewhere on the board
HT_SDATA: ISO1.7 (VO_F); also elsewhere on the board
ISO_GND: AD2.2 (GND), C5.2, C21.2, C34.2, C57.2, C103.2, C105.2, ISO2.9 (GND2), U3.2 (V-), V2.2 (GND); also elsewhere on the board
ISO_SEC_DHB_HI: ISO2.15 (VO_A); also elsewhere on the board
ISO_SEC_DHB_LO: ISO2.14 (VO_B); also elsewhere on the board
unnamed: AD1.4 (CLK), ISO1.11 (VO_E)
unnamed: AD1.6 (CS), ISO1.12 (VO_D)
unnamed: AD1.5 (SDATA), ISO1.10 (VI_F)
unnamed: AD1.1 (VA), C59.1, C83.1, C104.1, ISO1.16 (VDD2), U2.5 (V+), V3.5 (VOUT)
unnamed: AD1.3 (Vin), C7.1, R18.2
unnamed: AD2.4 (CLK), ISO2.11 (VO_E)
unnamed: AD2.6 (CS), ISO2.12 (VO_D)
unnamed: AD2.5 (SDATA), ISO2.10 (VI_F)
unnamed: AD2.3 (Vin), C5.1, R13.2
unnamed: D2.C (K), D3.A
unnamed: C13.1, D3.C (K), V3.1 (VIN), V3.3 (EN)
unnamed: R13.1, R113.2, U3.1
unnamed: R18.1, R122.2, U2.1
unnamed: R121.1, R122.1, U2.4 (-)
unnamed: C34.1, V2.4 (NR)
unnamed: C78.1, V3.4 (NR)
SYNCH_1: ISO1.3 (VI_B); also elsewhere on the board
SYNCH_2: ISO1.4 (VI_C); also elsewhere on the board

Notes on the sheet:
Primary (MCU side)
Secondary (isolated side)
Pin compatible with MAX11110, ADS7886 S/H, ADS7883 S/H (PDF note on the ADC).
V5.1 (PDF hand note). 5.2: ISO1 / ISO2 = CA-IS3761LW (Si8661 pinout, default low); ISO2 channel C carries DAB_DIS -> DAB_DIS_SEC (DRV6 DISABLE).
PDF aliases: SEC_GND = ISO_GND, HT_AUX = 6V3, AD2_3v3 = AD2_3V3; lowercase labels = IPC names.
The HT rail (ISO1 VDD2, AD1 VA, U2 V+, V3 VOUT, C59/C104/C83) is an unnamed net in Proteus (#00086): plain wire.
6V3 and HT_GND have their PWR_FLAGs on sheet 6 (terminals HT_6V3 / HT_GND).
The PWR_FLAG on V3 VIN is permanent (the net is fed by D3 and C13 only).
